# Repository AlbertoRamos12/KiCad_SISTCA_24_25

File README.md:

# KiCad_SISTCA_24_25
A collection of KiCad projects developed throughout a technical report, aimed at helping students study PCB design and circuit schematics through concrete examples.

# KiCad Project Collection – Learning Examples

This repository contains three KiCad projects developed as part of a technical report, aiming to support students in learning electronic circuit design and PCB layout using KiCad.

## 📁 Contents

The repository includes the following projects:

- **Example – Audio Amplifier Circuit:** Demonstrates the creation of a simple analog amplification circuit, focusing on schematic design and basic PCB layout.
- **Exercise – Boost Converter:** A DC-DC converter design with attention to component selection and layout for switching circuits.
- **Challenge – USBASP Programmer:** A more complex digital circuit with USB interface, intended to simulate a real-world PCB development scenario.

Each folder includes the full KiCad project files, including schematics, PCB layouts, and any custom libraries used during development.

## 🎯 Purpose

These projects were developed during the creation of a technical report and are made available here so that students can consult and learn from them. Whether revisiting concepts that were not fully understood or seeking concrete examples to support theory, these files offer practical insight into real circuit design using KiCad.

They are intended to help students:

- Understand the process of schematic capture and PCB design.
- Perform Electrical Rule Checks (ERC) and Design Rule Checks (DRC).
- Learn how to manage layout, routing, and component organization.
- Explore progressively complex circuits, from analog to digital.

## 👥 Authors

This work was developed by:

- José Ramos — 1221165  
- Gonçalo Vasconcelos — 1221163  
- Rafael Gonçalves — 1221169  
- Daniel Lima — 1221389  

**Supervisor:** José Diogo Dias (JDD)

## 🛠️ Requirements

- [KiCad](https://www.kicad.org/) version **9.0** or newer  
  > ⚠️ Note: Two of the three projects were created using KiCad 9, so compatibility with earlier versions is not guaranteed.
- Basic knowledge of electronics and schematic interpretation

## 📚 License

This repository is intended for educational purposes. Users are encouraged to explore, adapt, and reuse the contents for their own learning and academic work.

---

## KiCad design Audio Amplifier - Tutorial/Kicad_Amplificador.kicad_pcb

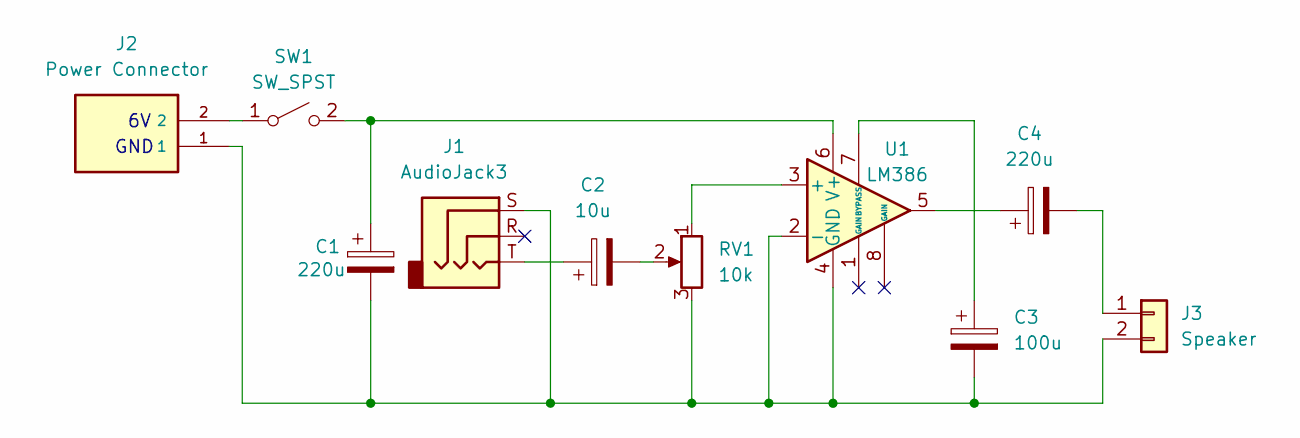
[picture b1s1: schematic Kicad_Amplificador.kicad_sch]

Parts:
C1, C4: 220u; CP_Radial_D8.0mm_P3.50mm
C2: 10u; C_1206_3216Metric
C3: 100u; CP_Radial_D5.0mm_P2.00mm
J1: AudioJack3; Jack_3.5mm_CUI_SJ1-3523N_Horizontal
J2: Power Connector; OST_OSTTA020161
J3: Speaker; PinHeader_1x02_P2.54mm_Vertical
RV1: 10k; Potentiometer_Runtron_RM-065_Vertical
SW1: SW_SPST; SW_DIP_SPSTx01_Slide_9.78x4.72mm_W7.62mm_P2.54mm
U1: LM386; DIP-8_W7.62mm_Socket_LongPads

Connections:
unnamed: C2.1, J1.T
unnamed: C2.2, RV1.2
unnamed: C4.1, U1.5
unnamed: C4.2, J3.1
unnamed: C1.2, C3.2, J1.S, J2.1, J3.2, RV1.3, U1.2 (-), U1.4 (GND)
unnamed: J2.2, SW1.1 (A)
unnamed: C1.1, SW1.2 (B), U1.6 (V+)
unnamed: RV1.1, U1.3 (+)
unnamed: C3.1, U1.7 (BYPASS)

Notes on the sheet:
GND

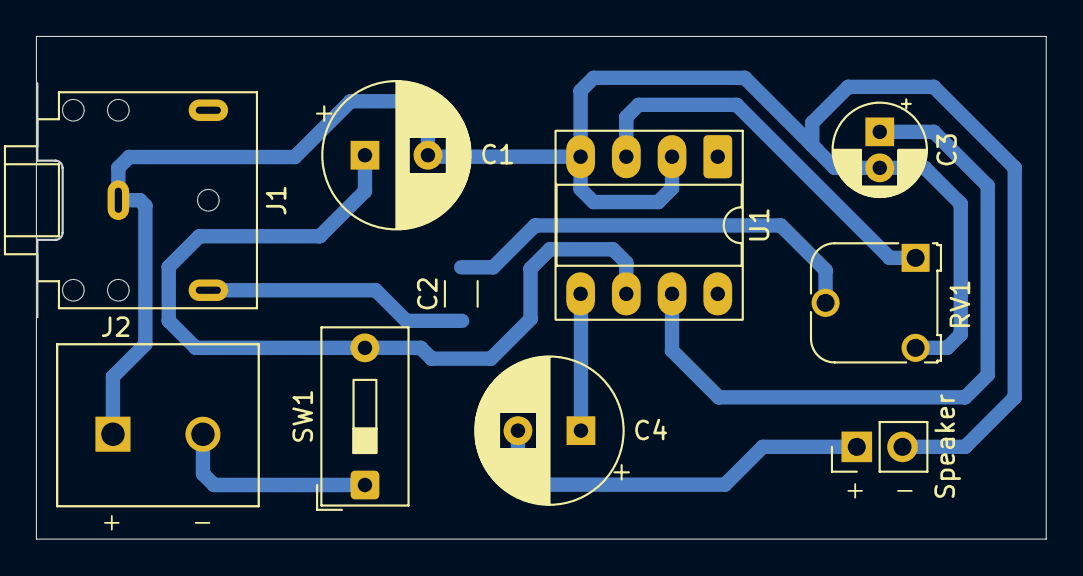
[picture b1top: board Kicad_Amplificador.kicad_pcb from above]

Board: 2 copper layers, 56.1 x 27.9 mm, 10 parts (0 on the bottom side), 9 nets.

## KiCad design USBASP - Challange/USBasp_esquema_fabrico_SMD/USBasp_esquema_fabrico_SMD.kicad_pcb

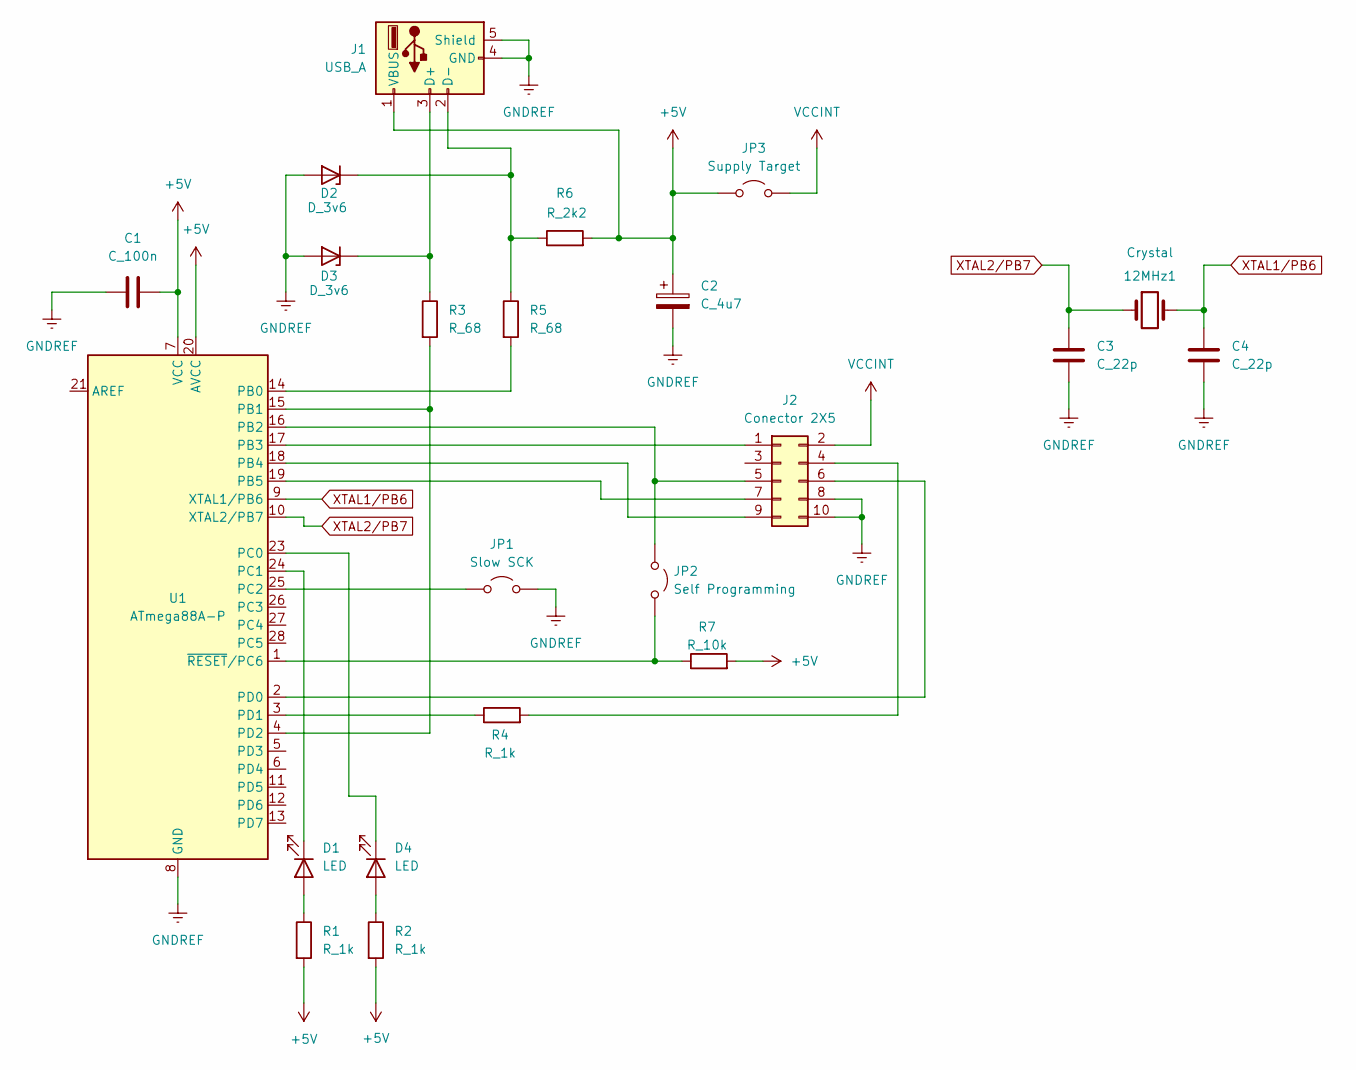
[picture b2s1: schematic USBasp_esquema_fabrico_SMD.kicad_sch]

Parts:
12MHz1: Crystal; Crystal_SMD_0603-4Pin_6.0x3.5mm
C1: C_100n; C_0603_1608Metric
C2: C_4u7; CP_EIA-3528-21_Kemet-B
C3, C4: C_22p; C_0603_1608Metric
D1, D4: LED; LED_0201_0603Metric
D2, D3: D_3v6; D_SOD-123
J1: USB_A; USB_A_CNCTech_1001-011-01101_Horizontal
J2: Conector 2X5; IDC-Header_2x05_P2.54mm_Vertical
JP1: Slow SCK; PinHeader_1x02_P2.54mm_Vertical
JP2: Self Programming; PinHeader_1x02_P2.54mm_Vertical
JP3: Supply Target; PinHeader_1x02_P2.54mm_Vertical
R1, R2: R_1k; R_0402_1005Metric
R3, R5: R_68; R_0603_1608Metric
R4: R_1k; R_0603_1608Metric
R6: R_2k2; R_0603_1608Metric
R7: R_10k; R_0603_1608Metric
U1: ATmega88A-P; DIP-28_W7.62mm

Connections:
+5V: C1.2, C2.1, J1.1 (VBUS), JP3.1 (A), R1.2, R2.2, R6.2, R7.2, U1.7 (VCC), U1.20 (AVCC)
GNDREF: C1.1, C2.2, C3.2, C4.2, D2.2 (A), D3.2 (A), J1.4 (GND), J1.5 (Shield), J2.8, J2.10, JP1.2 (B), U1.8 (GND), U1.22 (GND)
unnamed: D1.2 (A), R1.1
unnamed: D1.1 (K), U1.24 (PC1)
unnamed: D2.1 (K), J1.2 (D-), R5.1, R6.1
unnamed: D3.1 (K), J1.3 (D+), R3.1
unnamed: D4.2 (A), R2.1
unnamed: D4.1 (K), U1.23 (PC0)
unnamed: J2.1, U1.17 (PB3)
unnamed: J2.4, R4.2
unnamed: J2.5, JP2.1 (A), U1.16 (PB2)
unnamed: J2.6, U1.2 (PD0)
unnamed: J2.7, U1.19 (PB5)
unnamed: J2.9, U1.18 (PB4)
unnamed: JP1.1 (A), U1.25 (PC2)
unnamed: JP2.2 (B), R7.1, U1.1 (~RESET/PC6)
unnamed: R5.2, U1.14 (PB0)
unnamed: R3.2, U1.4 (PD2), U1.15 (PB1)
unnamed: R4.1, U1.3 (PD1)
VCCINT: J2.2, JP3.2 (B)
XTAL1/PB6: 12MHz1.2, C4.1, U1.9 (XTAL1/PB6)
XTAL2/PB7: 12MHz1.1, C3.1, U1.10 (XTAL2/PB7)

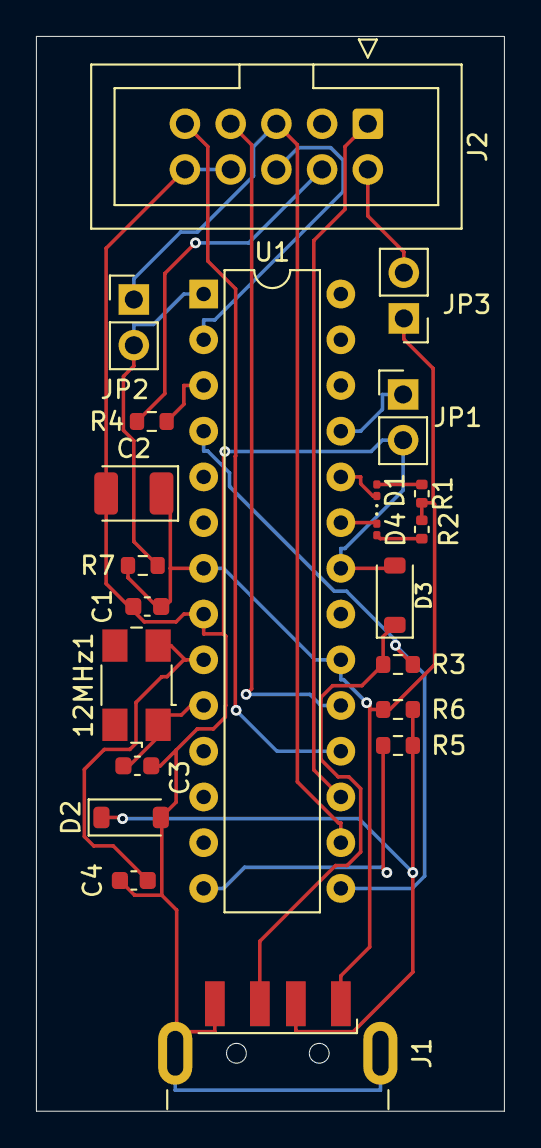
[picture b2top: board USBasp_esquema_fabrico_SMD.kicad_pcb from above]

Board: 2 copper layers, 26.0 x 59.7 mm, 22 parts (0 on the bottom side), 22 nets.

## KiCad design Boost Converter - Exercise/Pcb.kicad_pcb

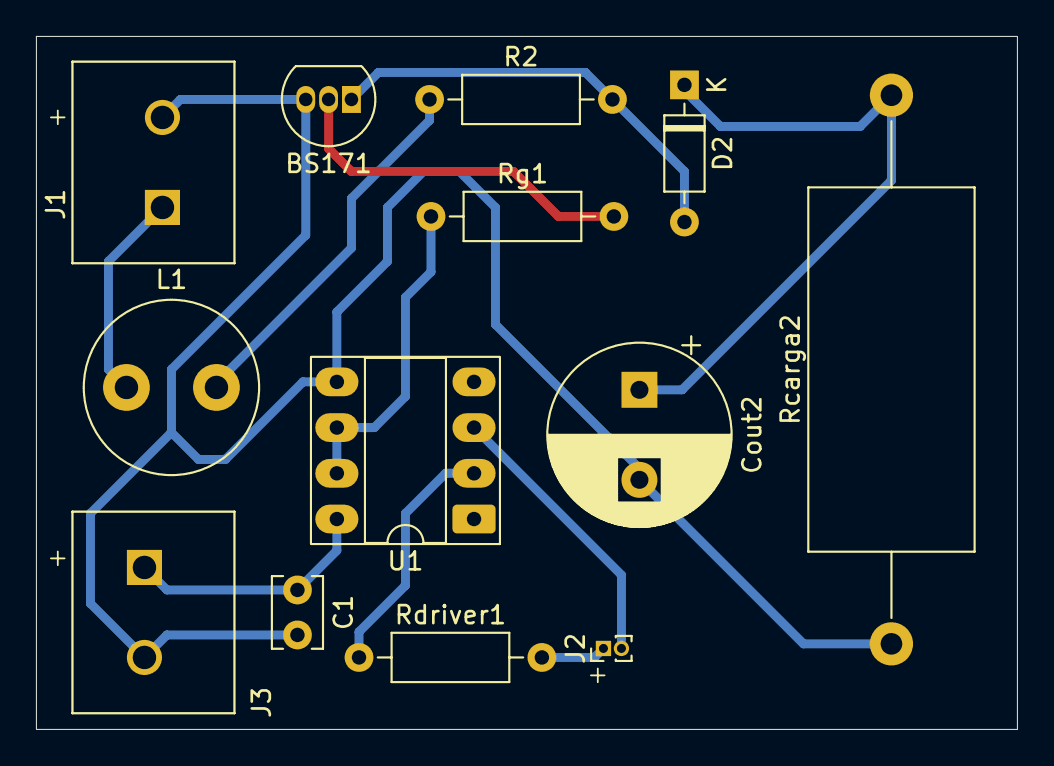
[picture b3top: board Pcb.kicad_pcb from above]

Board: 2 copper layers, 54.5 x 38.5 mm, 13 parts (0 on the bottom side), 11 nets.

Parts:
BS171: TO-92_Inline
C1: 0.1 uF; C_Disc_D3.8mm_W2.6mm_P2.50mm
Cout2: 160 uF; CP_Radial_D10.0mm_P5.00mm
D2: D_DO-35_SOD27_P7.62mm_Horizontal
J1: 12 V; OST_OSTTA020161
J2: PWM 5 V; PinHeader_1x02_P1.00mm_Vertical
J3: 15 V; OST_OSTTA020161
L1: 4.7 mH; L_Radial_D9.5mm_P5.00mm_Fastron_07HVP
R2: 0.33 Ω; R_Axial_DIN0207_L6.3mm_D2.5mm_P10.16mm_Horizontal
Rcarga2: 100 Ω; R_Axial_DIN0922_L20.0mm_D9.0mm_P30.48mm_Horizontal
Rdriver1: 500; R_Axial_DIN0207_L6.3mm_D2.5mm_P10.16mm_Horizontal
Rg1: 12 Ω; R_Axial_DIN0207_L6.3mm_D2.5mm_P10.16mm_Horizontal
U1: DIP-8_W7.62mm_Socket_LongPads

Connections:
/Drain: BS171.1 (D), D2.2 (A), R2.2
/Gate: BS171.2 (G), Rg1.2
/Source: BS171.3 (S), C1.2, Cout2.2, J1.2, J3.2, Rcarga2.1, U1.5 (GND)
unnamed: Cout2.1, D2.1 (K), Rcarga2.2
unnamed: J1.1, L1.1
unnamed: J2.1, Rdriver1.2
unnamed: J2.2, U1.3 (Cathode)
unnamed: L1.2, R2.1
unnamed: Rg1.1, U1.6 (Vo), U1.7 (Vo)
unnamed: Rdriver1.1, U1.2 (Anode)
unnamed: C1.1, J3.1, U1.8 (VCC)

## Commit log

2025-04-29 added folders
2025-05-03 adicao ficheiros
2025-05-03 adição elevador
2025-05-03 gerbers
